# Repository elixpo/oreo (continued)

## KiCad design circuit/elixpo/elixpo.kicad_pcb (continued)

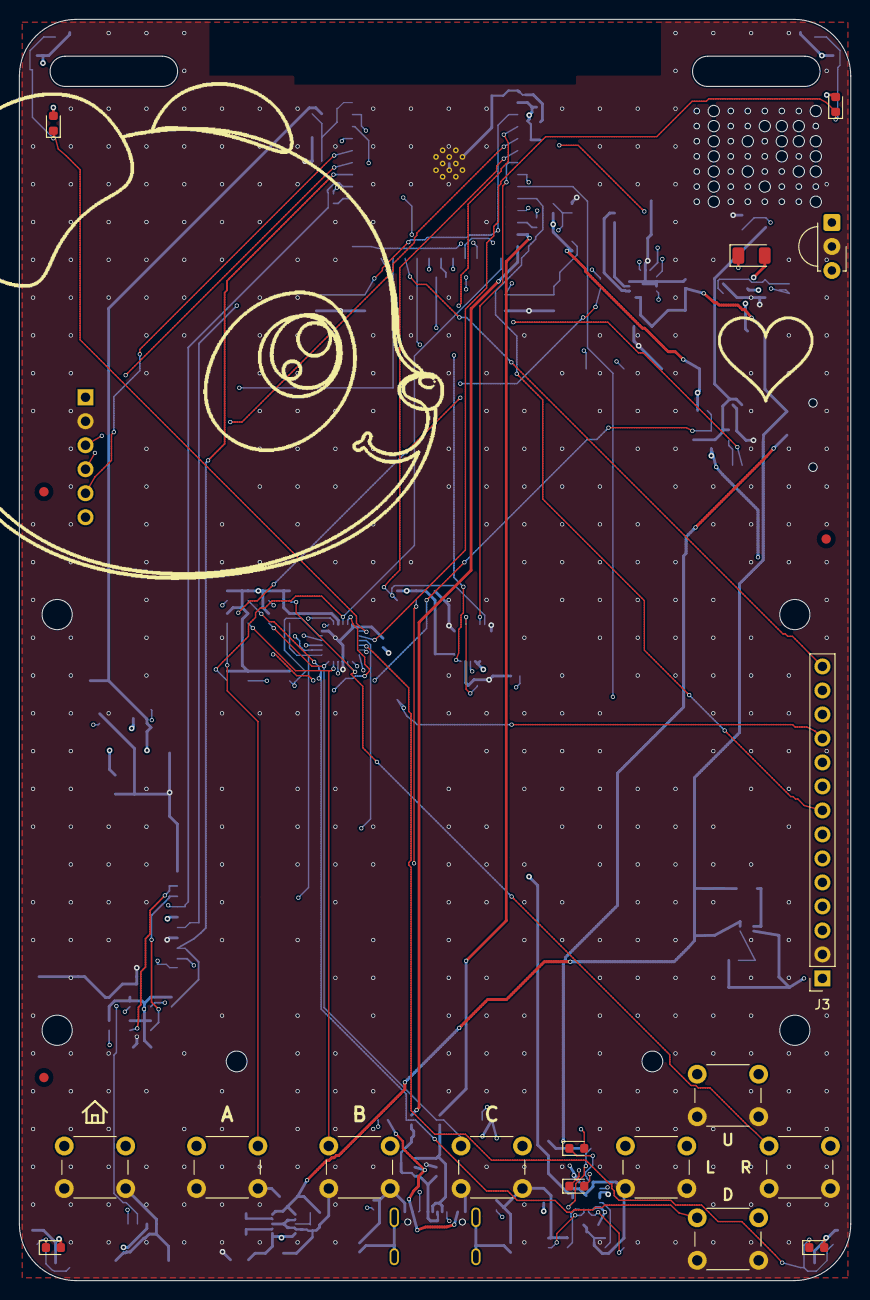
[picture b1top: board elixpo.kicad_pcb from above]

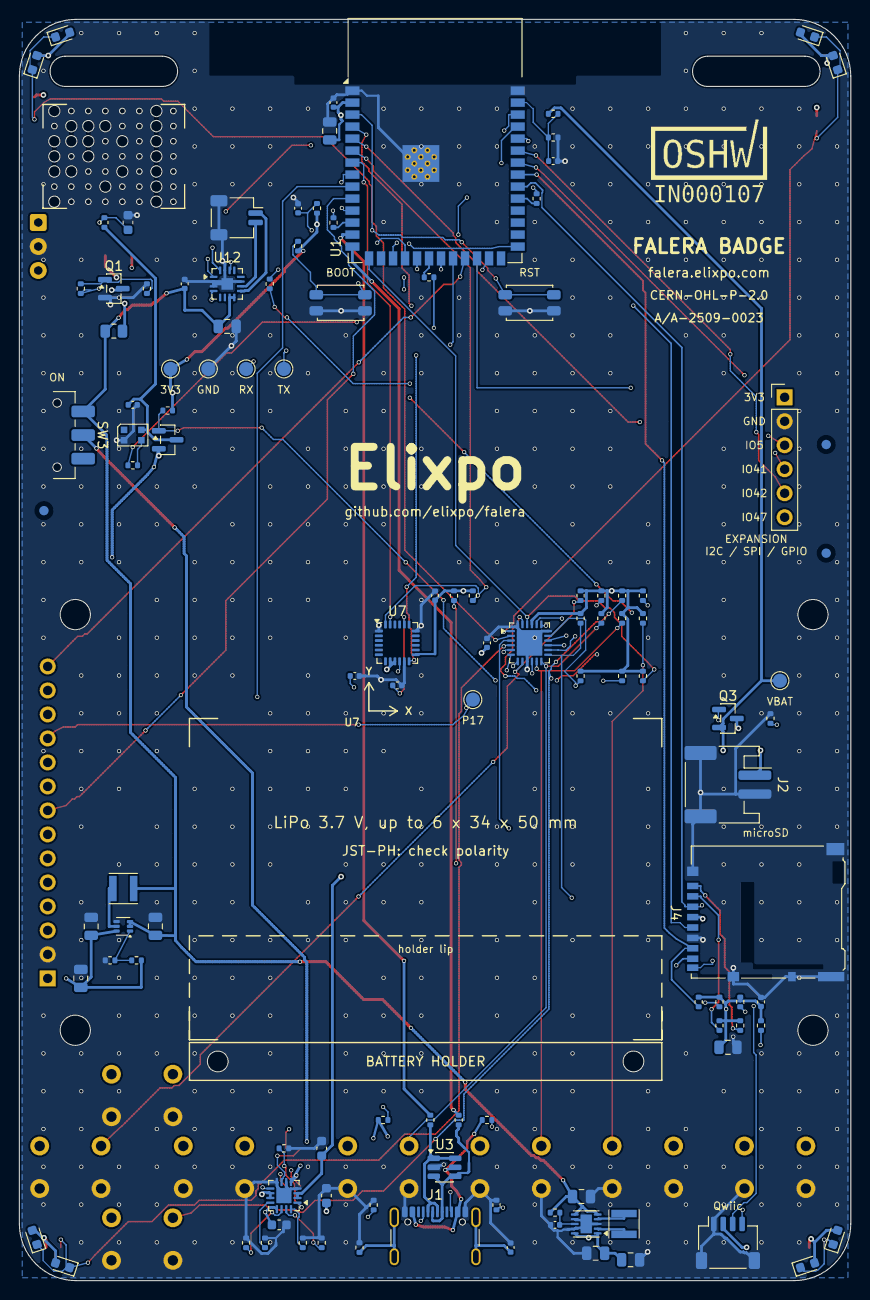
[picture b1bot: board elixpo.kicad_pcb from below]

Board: 4 copper layers, 88.0 x 133.5 mm, 141 parts (114 on the bottom side), 94 nets.

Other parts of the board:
C31: 10uF 10V; C_0805_2012Metric
C32: 22uF 10V; C_0805_2012Metric
FID1, FID2, FID3, FID4, FID5, FID6: Fiducial_1mm_Mask2mm
G1: speaker grille
H1, H2, H3, H4: MountingHole_3.2mm_M3
H5, H6: MountingHole_2.2mm_M2
L2: 1.5uH 2A shielded; L_Taiyo-Yuden_NR-30xx
Q4: AO3401A; SOT-23
R20: 150k 1%; R_0402_1005Metric
R21: 20k 1%; R_0402_1005Metric
R46: 100k; R_0402_1005Metric
U6: TPS61023 5V boost; SOT-563

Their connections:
AUX_ON_N: Q4.1, R46.1; also elsewhere on the board
GND: C31.2, C32.2, R21.2, U6.4; also elsewhere on the board
LCD_5V: C32.1, R20.1, U6.6; also elsewhere on the board
LCD_BOOST_SW: L2.2, U6.5
LCD_FB: R20.2, R21.1, U6.1
VSYS_SW: C31.1, L2.1, U6.2, U6.3; also elsewhere on the board

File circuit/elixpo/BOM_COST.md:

# Oreo badge: one-unit BOM and cost

The cost of the parts in **one** badge, from the prices actually paid on 17 November 2026. Both orders were charged at ₹93.96 to the dollar (JLCPCB ₹4,122 for $43.87; LCSC ₹4,063 for $43.24), so every LCSC price below is converted at that rate. Each LCSC line is the quantity one badge uses multiplied by that part's one-unit price in the cart; the packs and spare chips bought are not counted.

## Summary

| | Cost |
|---|--:|
| Bare board (1 of 5) | ₹824.40 |
| LCSC parts, 50 lines (section 2) | ₹1,799.37 |
| LCSC shipping, this badge's share | ₹90.93 |
| Bought separately (section 3) | ₹1,457.00 |
| **One badge** | **₹4,171.70** |
| With a ±2% margin | ₹4,088 – ₹4,255 |

Not included: customs duty on the two imports (paid on delivery; add its per-badge share when it is known), the soldering tools, and labour.

## 1. Board

JLCPCB, 5 bare boards for $43.87 = ₹4,122 including shipping, after a $6 first-order discount: 4 layers, FR-4 TG135, 1.6 mm, black mask, white silkscreen, HASL, 0.3 mm plugged vias, flying-probe tested. **One board: ₹824.40.**

## 2. Parts from LCSC

| Where it goes | Part | LCSC | Qty | Unit | Line |
|---|---|---|--:|--:|--:|
| C1 C21 C28 C32 | Samsung CL21A226MAYNNNE, 22 uF 25 V X5R 0805 | C602037 | 4 | ₹10.12 | ₹40.48 |
| C2 C22 C27 C40 C61 C62 C64 C68 C71 | Samsung CL05B104KO5NNNC, 100 nF 16 V X7R 0402 | C1525 | 9 | ₹0.23 | ₹2.03 |
| C3 | Samsung CL05A105KA5NQNC, 1 uF 25 V X5R 0402 | C52923 | 1 | ₹0.53 | ₹0.53 |
| C20 C30 C31 C60 C67 | Samsung CL21A106KAYNNNE, 10 uF 25 V X5R 0805 | C15850 | 5 | ₹2.95 | ₹14.75 |
| C23 | FH 0402B102K500NT, 1 nF 50 V X7R 0402 | C1523 | 1 | ₹0.34 | ₹0.34 |
| C24 | Taiyo Yuden UMK107BJ105KA-T, 1 uF 50 V X5R 0603 | C92848 | 1 | ₹3.13 | ₹3.13 |
| C25 C26 C70 | Samsung CL10A475KO8NNNC, 4.7 uF 16 V X5R 0603 | C19666 | 3 | ₹1.42 | ₹4.26 |
| Q1 | CJ MMBT2222A, NPN SOT-23 | C8512 | 1 | ₹1.72 | ₹1.72 |
| Q3 Q4 | AOS AO3401A, P-MOSFET SOT-23 | C15127 | 2 | ₹7.71 | ₹15.43 |
| R1 R2 R16 R27 R42 R43 R45 R50 R51 R52 R53 R54 R55 R56 R57 R62 R63 R64 R65 R66 R67 | YAGEO RC0402JR-0710KL, 10 k 0402 | C60489 | 21 | ₹0.18 | ₹3.75 |
| R3 R4 R12 R13 | YAGEO RC0402FR-0722RL, 22 R 0402 | C114765 | 4 | ₹0.17 | ₹0.68 |
| R5 | UNI-ROYAL 0402WGF330JTCE, 33 R 0402 | C25105 | 1 | ₹0.11 | ₹0.11 |
| R10 R11 | UNI-ROYAL 0402WGF5101TCE, 5.1 k 1% 0402 | C25905 | 2 | ₹0.13 | ₹0.26 |
| R14 R15 | UNI-ROYAL 0402WGF2001TCE, 2 k 1% 0402 | C4109 | 2 | ₹0.18 | ₹0.36 |
| R17 R18 R46 R72 | UNI-ROYAL 0402WGF1003TCE, 100 k 1% 0402 | C25741 | 4 | ₹0.08 | ₹0.34 |
| R19 R60 | UNI-ROYAL 0402WGF1004TCE, 1 M 1% 0402 | C26083 | 2 | ₹0.11 | ₹0.23 |
| R21 | UNI-ROYAL 0402WGF2002TCE, 20 k 1% 0402 | C25765 | 1 | ₹0.09 | ₹0.09 |
| R22 | UNI-ROYAL 0402WGF4702TCE, 47 k 1% 0402 | C25792 | 1 | ₹0.18 | ₹0.18 |
| R23 R24 R71 | UNI-ROYAL 0402WGF1001TCE, 1 k 1% 0402 | C11702 | 3 | ₹0.12 | ₹0.37 |
| R25 | UNI-ROYAL 0402WGF3301TCE, 3.3 k 1% 0402 | C25890 | 1 | ₹0.34 | ₹0.34 |
| R26 | UNI-ROYAL 0402WGF100JTCE, 10 R 0402 | C25077 | 1 | ₹0.10 | ₹0.10 |
| R40 R41 | UNI-ROYAL 0402WGF2201TCE, 2.2 k 1% 0402 | C25879 | 2 | ₹0.11 | ₹0.23 |
| R70 | UNI-ROYAL 0402WGF1000TCE, 100 R 1% 0402 | C25076 | 1 | ₹0.11 | ₹0.11 |
| R73 | UNI-ROYAL 0805W8F470JT5E, 47 R 0805 | C17714 | 1 | ₹0.25 | ₹0.25 |
| R74 | UNI-ROYAL 0402WGF3300TCE, 330 R 1% 0402 | C25104 | 1 | ₹0.10 | ₹0.10 |
| C63 | FH 0402B222K500NT, 2.2 nF 50 V X7R 0402 | C1531 | 1 | ₹0.23 | ₹0.23 |
| D1 D2 D3 D4 D21 D30 D31 D32 D33 D34 D35 D36 D37 | KENTO KT-0603O, orange (598 nm) 0603 | C111340 | 13 | ₹1.11 | ₹14.41 |
| D10 | Vishay VSMY2940GX01, 940 nm 1206 | C3202699 | 1 | ₹72.33 | ₹72.33 |
| D20 | KENTO KT-0603G, green 0603 | C12624 | 1 | ₹1.13 | ₹1.13 |
| J1 | GCT USB4105-GF-A, USB-C receptacle | C3020560 | 1 | ₹96.93 | ₹96.93 |
| J2 | XYECONN XY-S2B-PH-SM4-TB, JST-PH 2-pin battery connector | C54582899 | 1 | ₹4.44 | ₹4.44 |
| J4 | Hirose DM3AT-SF-PEJM5, microSD | C114218 | 1 | ₹131.94 | ₹131.94 |
| J5 | JST SM04B-SRSS-TB(LF)(SN), SH 4-pin | C51940130 | 1 | ₹3.72 | ₹3.72 |
| J7 | JST SM02B-SRSS-TB(LF)(SN), SH 2-pin (speaker plug) | C160402 | 1 | ₹12.54 | ₹12.54 |
| L1 L2 | TDK VLS3015ET-1R5N, 1.5 uH | C3221497 | 2 | ₹5.94 | ₹11.88 |
| R20 | UNI-ROYAL 0402WGF1503TCE, 150 k 1% 0402 | C25755 | 1 | ₹0.10 | ₹0.10 |
| SW1 SW2 | Panasonic EVQP2P02W, side-push tact (reset, boot) | C512395 | 2 | ₹52.98 | ₹105.95 |
| SW3 | C&K JS102011SAQN, slide switch | C221660 | 1 | ₹81.03 | ₹81.03 |
| U1 | Espressif ESP32-S3-WROOM-1-N16R8 | C2913202 | 1 | ₹507.40 | ₹507.40 |
| U3 | ST USBLC6-2SC6, USB ESD | C7519 | 1 | ₹14.89 | ₹14.89 |
| U4 | TI BQ24074RGTR, charger, VQFN-16 | C54313 | 1 | ₹201.00 | ₹201.00 |
| U5 | TI TPS63031DSKR, 3.3 V buck-boost, WSON-10 | C15516 | 1 | ₹109.73 | ₹109.73 |
| U6 | TI TPS61023DRLR, 5 V boost for the display, SOT-563 | C919459 | 1 | ₹22.11 | ₹22.11 |
| U9 | Worldsemi WS2812B-2020-V6, status LED | C52917434 | 1 | ₹8.67 | ₹8.67 |
| U11 | Awinic AW9523BTQR, I2C expander, QFN-24 | C148077 | 1 | ₹30.96 | ₹30.96 |
| U12 | ADI MAX98357AETE+T, I2S amplifier, TQFN-16 | C910544 | 1 | ₹124.17 | ₹124.17 |
| J3 | 1x14 female header, 2.54 mm, 8.5 mm tall | C41417326 | 1 | ₹22.24 | ₹22.24 |
| SW11 SW12 SW13 SW14 SW15 SW16 SW17 SW18 | SHOU HAN TS665CJ, 6x6x5 mm through-hole button | C393938 | 8 | ₹1.84 | ₹14.73 |
| U8 | Vishay TSOP38238, 38 kHz IR receiver | C141632 | 1 | ₹61.47 | ₹61.47 |
| LS1 | XHXDZ 1511-L60MM, 8 ohm 15x11 mm speaker | C50387185 | 1 | ₹55.19 | ₹55.19 |
| | **Parts** | | | | **₹1,799.37** |
| | Shipping share ($2.08 net shipping, split by value) | | | | ₹90.93 |
| | **LCSC total** | | | | **₹1,890.30** |

## 3. Bought separately

| Ref | Item | Qty | Price | Status |
|---|---|--:|--:|---|
| LCD1 | 2.8″ ILI9341 SPI display with touch, 14-pin (MSP2807 type) | 1 | ₹629 | paid |
| U7 | MPU-6050 motion sensor, QFN-24 4×4 mm | 1 | ₹426 | paid |
| BT1 | LiPo 3.7 V 2000 mAh, protection board, JST-PH 2.0 lead | 1 | ₹300 | paid |
| — | Photo paper name card for the front | 1 | ₹10 | paid |
| — | Lanyard | 1 | ₹20 | paid |
| HW1–HW14 | 4 × M3 11 mm standoffs, 8 × M3×5 and 2 × M2×6 screws | 1 | ₹62 | estimate |
| BH1 | Battery mount (double-sided foam tape) | 1 | ₹10 | estimate |
| | **Total** | | **₹1,457** | |

## Notes

- Totals carry a ±2% margin for exchange-rate and price changes.

- The two `estimate` lines are the only prices not yet paid; replace them when bought.
- Spares bought with the first order (a second BQ24074 and TPS63031, and the rest of each pack) are not in this cost.
- The full BOM with every designator is `BOM_ORDER.csv`.

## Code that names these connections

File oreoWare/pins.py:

"""GPIO assignments for the Falera Badge: the breadboard prototype, then the PCB.

Single source of truth. Every hardware module imports from here — never hardcode a
GPIO number anywhere else. When the PCB swaps pins, this is the only file to edit.
"""

# ----- Display: SmartElex 2.0" IPS, ST7789P3, 4-wire SPI -----
# Module silkscreen → our name:  CS=CS, RST=RESET, DC=DC, SDA=MOSI, SCL=SCK, EN=BL
# Power: VCC → DevKit 5V pin (module has onboard 3V3 LDO). TE pin left disconnected.
DISPLAY_CS    = 14
DISPLAY_RESET = 16
DISPLAY_DC    = 15
DISPLAY_MOSI  = 11     # display silkscreen: SDA
DISPLAY_SCK   = 12     # display silkscreen: SCL
DISPLAY_BL    = 17     # display silkscreen: EN. Active-high, PWM-capable for brightness
DISPLAY_BAUD  = 40_000_000  # 40MHz SPI. Each full framebuf transfer is
                            # 320×240×2 = 153,600 bytes → ~30.7 ms on the wire.
                            # 40 MHz is the practical ceiling for GPIO-matrix-
                            # routed pins on ESP32-S3 (MOSI=11, SCK=12 aren't
                            # on the IO_MUX — going higher loses bits at the
                            # GPIO matrix). Combined with the 4-chunk write
                            # and proper 5V power, this is stable.

# ----- Buttons (active-low, internal pull-up) -----
BTN_HOME   = 9
BTN_A      = 10
BTN_B      = 13
BTN_C      = 8
BTN_UP     = 4
BTN_DOWN   = 5
BTN_LEFT   = 6
BTN_RIGHT  = 7

# ----- microSD (SDMMC host, 1-bit, the host's own DMA) -----
# Breadboard: a plain 3.3 V microSD breakout (no level shifter; the blue
# 5 V SPI modules buffer the lines one way and cannot do SDMMC). CMD and D0
# need 10 kΩ pull-ups to 3V3 (most breakouts have them). Its own bus, so the
# card never shares the display's SPI bus. These pins were the corner LEDs,
# which were never wired or driven; they move to the I2C expander or the PCB
# (#102).
SD_CLK = 38
SD_CMD = 39
SD_D0  = 40

# ----- I2S speaker amplifier (MAX98357A) -----
# BCLK/LRCLK/DIN only; the amp's SD pin to VIN (always on, L+R mix), GAIN
# floating (9 dB). VIN from the 5 V rail, not the 3.3 V regulator.
# GPIO46 is a boot-strapping pin: it must read low at reset and while
# flashing. The amp's DIN is a high-impedance input and the pin's internal
# pull-down keeps it low until I2S starts, so add no pull-up on this line.
I2S_BCLK  = 41
I2S_LRCLK = 21
I2S_DOUT  = 46

# ----- Status NeoPixel (onboard WS2812) -----
LED_STATUS = 48

# ----- IR subsystem -----
# Reassigned from BOM's original GPIO48 because that pin is the onboard NeoPixel.
# Picked from the unused pool: 2, 18, 21, 42, 47.
IR_TX = 2     # to 2N2222 base via 4.7kΩ
IR_RX = 18    # TSOP38238 OUT pin

# ----- Analog inputs -----
ADC_VBAT = 1  # ADC1_CH0, fed by the 100kΩ/100kΩ divider stub

# ----- I2C bus (shared by MPU6050; future expanders) -----
# Picked from the unused pool: 42, 47 are general-purpose, non-strapping,
# not on PSRAM lines for N16R8, and not USB-OTG pads.
I2C_SDA   = 42
I2C_SCL   = 47

# ----- MPU6050 -----
# +Y axis of the IMU is wired to "up" on the screen (the way the user holds
# the badge horizontally during the racer game). Mount in-plane with the
# board so pitch = front/back tilt, roll = side-to-side tilt, yaw = twist.
IMU_INT   = 3      # RTC_GPIO3 — wakes from deep sleep on a motion interrupt

# ----- TTP223 touch pads (not fitted) -----
# The planned pads were never wired or read. Their pins went elsewhere:
# GPIO21 is I2S LRCLK, and GPIO33 is not on the DevKit header at all (inside
# the N16R8 module it belongs to the octal PSRAM bus). Pick new pins for
# touch on the expander or the PCB (#102).


# ═════ PCB badge (circuit/elixpo/) ══════════════════════════════════════
# The values above are the breadboard's. On the PCB badge, which
# oreoWare.board detects from its AW9523B expander, the pins below
# replace them. The display (11, 12, 14-17), microSD (38-40), IR (2, 18),
# status LED (48) and battery sense (1) keep the same GPIOs.
try:
    from oreoWare import board as _board
    BOARD = _board.board()
except ImportError:
    BOARD = "breadboard"

DISPLAY_DRIVER = "st7789"
EXPANDER = False            # buttons on GPIOs (breadboard) or the AW9523B

if BOARD == "pcb":
    # 2.8" ILI9341 module (MSP2807 type) with an XPT2046 touch controller
    DISPLAY_DRIVER = "ili9341"
    DISPLAY_MISO   = 13     # the touch controller's data out; the LCD has none
    TOUCH_IRQ      = 21     # XPT2046 PENIRQ, active low; T_CS is EXP_TOUCH_CS
    # The buttons are on the expander, not on GPIOs.
    EXPANDER = True
    BTN_HOME = BTN_A = BTN_B = BTN_C = None
    BTN_UP = BTN_DOWN = BTN_LEFT = BTN_RIGHT = None
    # I2C: AW9523B 0x58 and MPU-6050 0x69 (AD0 high), 2.2 kΩ pull-ups
    I2C_SDA   = 6
    I2C_SCL   = 7
    EXP_ADDR  = 0x58
    EXP_INT   = 3           # AW9523B ~INT, active low, RTC GPIO: wakes the badge
    IMU_INT   = 4
    # MAX98357A; its SD_MODE is EXP_AMP_EN on the expander
    I2S_BCLK  = 8
    I2S_LRCLK = 9
    I2S_DOUT  = 10
    # J6 expansion header: 3V3, GND, then these, in this order
    EXPANSION = (5, 41, 42, 47)

# AW9523B pins (PCB only). Port 0 bit n is the button EXP_BUTTON_ORDER[n]
# names; port 1 holds the rest.
EXP_BUTTON_ORDER = ("UP", "DOWN", "LEFT", "RIGHT", "A", "B", "C", "HOME")
EXP_LED_BITS   = 0x0F       # P1_0-P1_3: corner LEDs TL, TR, BL, BR (LED mode only)
EXP_AMP_EN     = 1 << 4     # P1_4: high turns the speaker amp on
EXP_SD_DET     = 1 << 5     # P1_5: low when a card is in
EXP_AUX_ON_N   = 1 << 6     # P1_6: low powers the IR receiver and status LED
EXP_TOUCH_CS   = 1 << 7     # P1_7: the touch controller's chip select, active low

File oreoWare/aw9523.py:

"""AW9523B I2C expander on the PCB badge (0x58): buttons, corner LEDs,
amp enable, card detect, the switched 3.3 V supply and the touch chip select.

Port 0: the eight buttons (pins.EXP_BUTTON_ORDER), active low, with 10 kΩ
pull-ups on the board. Their interrupt is enabled, so ~INT (pins.EXP_INT)
goes low when one changes; reading port 0 clears it.

Port 1:
  P1_0-P1_3  corner LEDs. Each sinks the cathodes of three LEDs with no
             series resistor, so these pins only ever run in the chip's
             constant-current LED mode, never as GPIO outputs driven low.
  P1_4       AMP_EN, high = speaker amp on
  P1_5       SD_DET, input, low = card in
  P1_6       AUX_ON_N, low = IR receiver and status LED powered
  P1_7       touch controller chip select, high = deselected

get() returns the one shared instance on the PCB badge, set up on first
use, and None on the breadboard badge.
"""

from oreoWare import pins

ADDR = 0x58
CHIP_ID = 0x23

_IN0, _IN1 = 0x00, 0x01
_OUT0, _OUT1 = 0x02, 0x03
_CFG0, _CFG1 = 0x04, 0x05          # 1 = input
_INT0, _INT1 = 0x06, 0x07          # 0 = interrupt enabled
_ID = 0x10
_GCR = 0x11
_MODE0, _MODE1 = 0x12, 0x13        # 1 = GPIO, 0 = LED (constant current)
_DIM_P1 = (0x20, 0x21, 0x22, 0x23)  # current of P1_0..P1_3, 0-255

# GCR: ISEL = 11, a quarter of the 37 mA full scale (about 9 mA per channel,
# shared by the channel's three LEDs). Port 0 stays open-drain: it is all
# inputs.
_GCR_VALUE = 0x03

LED_TL, LED_TR, LED_BL, LED_BR = 0, 1, 2, 3


class AW9523:
    def __init__(self, i2c, addr=ADDR):
        self._i2c = i2c
        self._addr = addr
        self._b1 = bytearray(1)
        self._out1 = 0

    def _w(self, reg, value):
        self._b1[0] = value & 0xFF
        self._i2c.writeto_mem(self._addr, reg, self._b1)

    def _r(self, reg):
        self._i2c.readfrom_mem_into(self._addr, reg, self._b1)
        return self._b1[0]

    def chip_id(self):
        return self._r(_ID)

    def init(self):
        """Set every pin up. Safe to call again; it never turns a corner
        LED on, because the LED pins are held high until their current is
        zero and they are in LED mode."""
        self._w(_GCR, _GCR_VALUE)
        # LEDs off (pins high), amp off, AUX on (P1_6 low), touch deselected.
        self._out1 = pins.EXP_LED_BITS | pins.EXP_TOUCH_CS
        self._w(_OUT1, self._out1)
        self._w(_CFG1, pins.EXP_SD_DET)        # P1_5 input, the rest outputs
        for reg in _DIM_P1:
            self._w(reg, 0)
        self._w(_MODE1, 0xFF & ~pins.EXP_LED_BITS)   # P1_0-3 LED mode
        self._w(_MODE0, 0xFF)                  # port 0 GPIO
        self._w(_CFG0, 0xFF)                   # port 0 inputs
        self._w(_INT0, 0x00)                   # buttons interrupt
        self._w(_INT1, 0xFF)                   # port 1 doesn't
        self._r(_IN0)                          # clear a pending interrupt
        self._r(_IN1)

    # ── inputs ──────────────────────────────────────────────────────────
    def read_buttons(self):
        """Port 0 as a byte: bit n low = the button EXP_BUTTON_ORDER[n] is
        down. Also clears ~INT."""
        return self._r(_IN0)

    def card_present(self):
        return not (self._r(_IN1) & pins.EXP_SD_DET)

    # ── outputs ─────────────────────────────────────────────────────────
    def _set_out1(self, mask, on):
        v = (self._out1 | mask) if on else (self._out1 & ~mask)
        if v != self._out1:
            self._out1 = v
            self._w(_OUT1, v)

    def set_led(self, n, level):
        """Corner LED n (LED_TL..LED_BR) at 0-255."""
        if 0 <= n < 4:
            self._w(_DIM_P1[n], max(0, min(255, int(level))))

    def leds_off(self):
        for reg in _DIM_P1:
            self._w(reg, 0)

    def set_amp(self, on):
        self._set_out1(pins.EXP_AMP_EN, on)

    def set_aux(self, on):
        """Power the IR receiver and the status LED (P1_6 is active low)."""
        self._set_out1(pins.EXP_AUX_ON_N, not on)

    def set_touch_cs(self, selected):
        self._set_out1(pins.EXP_TOUCH_CS, not selected)


_dev = None


def get():
    """The PCB badge's expander, set up on first call; None elsewhere or
    when it doesn't answer."""
    global _dev
    if _dev is not None:
        return _dev
    if not getattr(pins, "EXPANDER", False):
        return None
    try:
        from machine import Pin, SoftI2C
        i2c = SoftI2C(scl=Pin(pins.I2C_SCL), sda=Pin(pins.I2C_SDA), freq=400_000)
        dev = AW9523(i2c, getattr(pins, "EXP_ADDR", ADDR))
        dev.init()
    except Exception:
        return None
    _dev = dev
    return dev
